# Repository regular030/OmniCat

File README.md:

# OMNICAT

For millions of us, Octocat has been a staple part of our lives, a hardworking and cheerful best friend. What would be more wonderful than to extend that friendship to the real world.
Go check out the journal for our progress and watch our youtube demo here!: https://www.youtube.com/watch?v=gtOdOln78Yw

What does omnicat do?

Feature 1: RC Car
Omnicat is a 4 wheel drive RC car that can be steered either by a traditional game controller or asynchronously through a Leap Motion Sensor with the gesture tracking bindings demonstrated in the video:
Open palm: forward; Fist: backward; Pointer: right; Peace: left; Hang Ten: mode switch

Feature 2: Git Desk Decoration
The OLED on the back displays live details about your Github that are important for easy access, such as number of stars or pull requests on a target repository. You can switch through the display modes using your controller/depth sensor.

Hello! This is our submission project for Hack Club's Highway Hackathon at Github HQ.
With the mission to build something intricate, wacky and helpful, we decided to build a personal home assistant: none other than Octocat itself!

## Wiring Diagram:

## File Structure:
- CAD
  - CAD/F3D Files for the project
- Firmware
  - The Firmware for this project
- new cad
  - STL and 3MF files for the chassis
 - Unity
   -  Unity files for hand Tracking

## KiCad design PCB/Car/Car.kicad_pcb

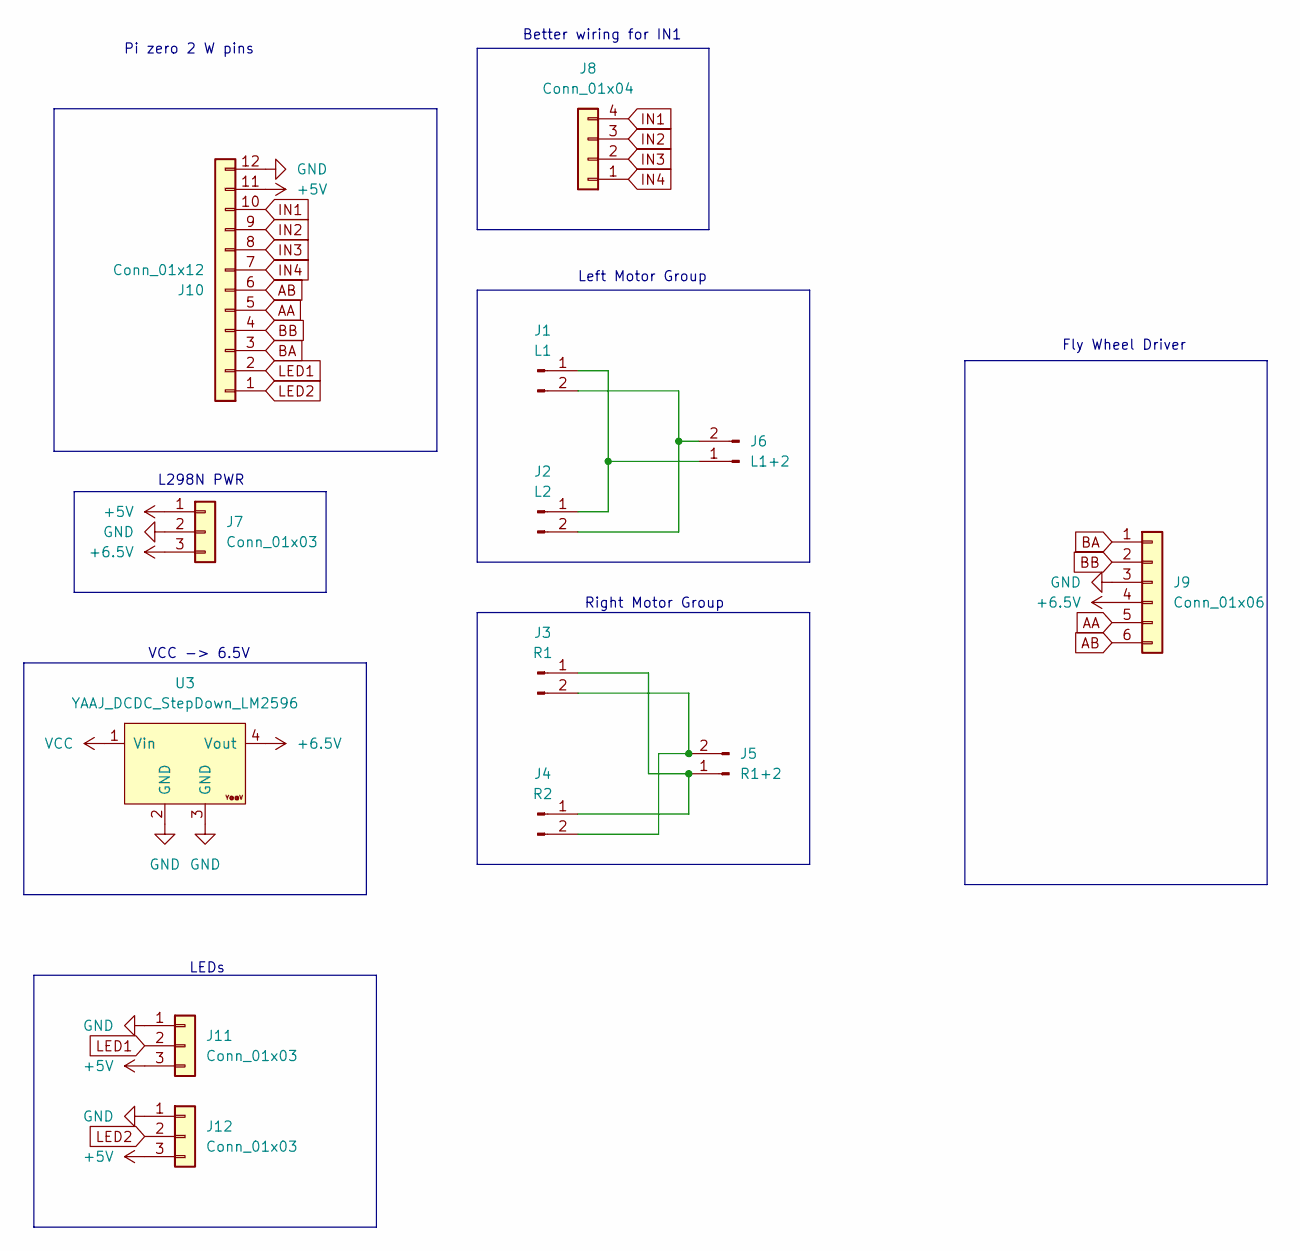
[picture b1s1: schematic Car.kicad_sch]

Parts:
J1: L1; JST 1x2
J2: L2; JST 1x2
J3: R1; JST 1x2
J4: R2; JST 1x2
J5: R1+2; JST 1x2
J6: L1+2; JST 1x2
J7, J11, J12: Conn_01x03; JST 1x3
J8: Conn_01x04; JST 1x4
J9: Conn_01x06; JST 1x6
J10: Conn_01x12; JST 1x12
U3: YAAJ_DCDC_StepDown_LM2596

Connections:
+5V: J7.1, J10.11, J11.3, J12.3
+6.5V: J7.3, J9.4, U3.4 (Vout)
AA: J9.5, J10.5
AB: J9.6, J10.6
BA: J9.1, J10.3
BB: J9.2, J10.4
GND: J7.2, J9.3, J10.12, J11.1, J12.1, U3.2 (GND), U3.3 (GND)
IN1: J8.4, J10.10
IN2: J8.3, J10.9
IN3: J8.2, J10.8
IN4: J8.1, J10.7
LED1: J10.2, J11.2
LED2: J10.1, J12.2
unnamed: J1.1, J2.1, J6.1
unnamed: J1.2, J2.2, J6.2
unnamed: J3.1, J4.1, J5.1
unnamed: J3.2, J4.2, J5.2
VCC: U3.1 (Vin)

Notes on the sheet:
Better wiring for IN1
Left Motor Group
Pi zero 2 W pins
Right Motor Group
VCC -> 6.5V
LEDs
L298N PWR
Fly Wheel Driver

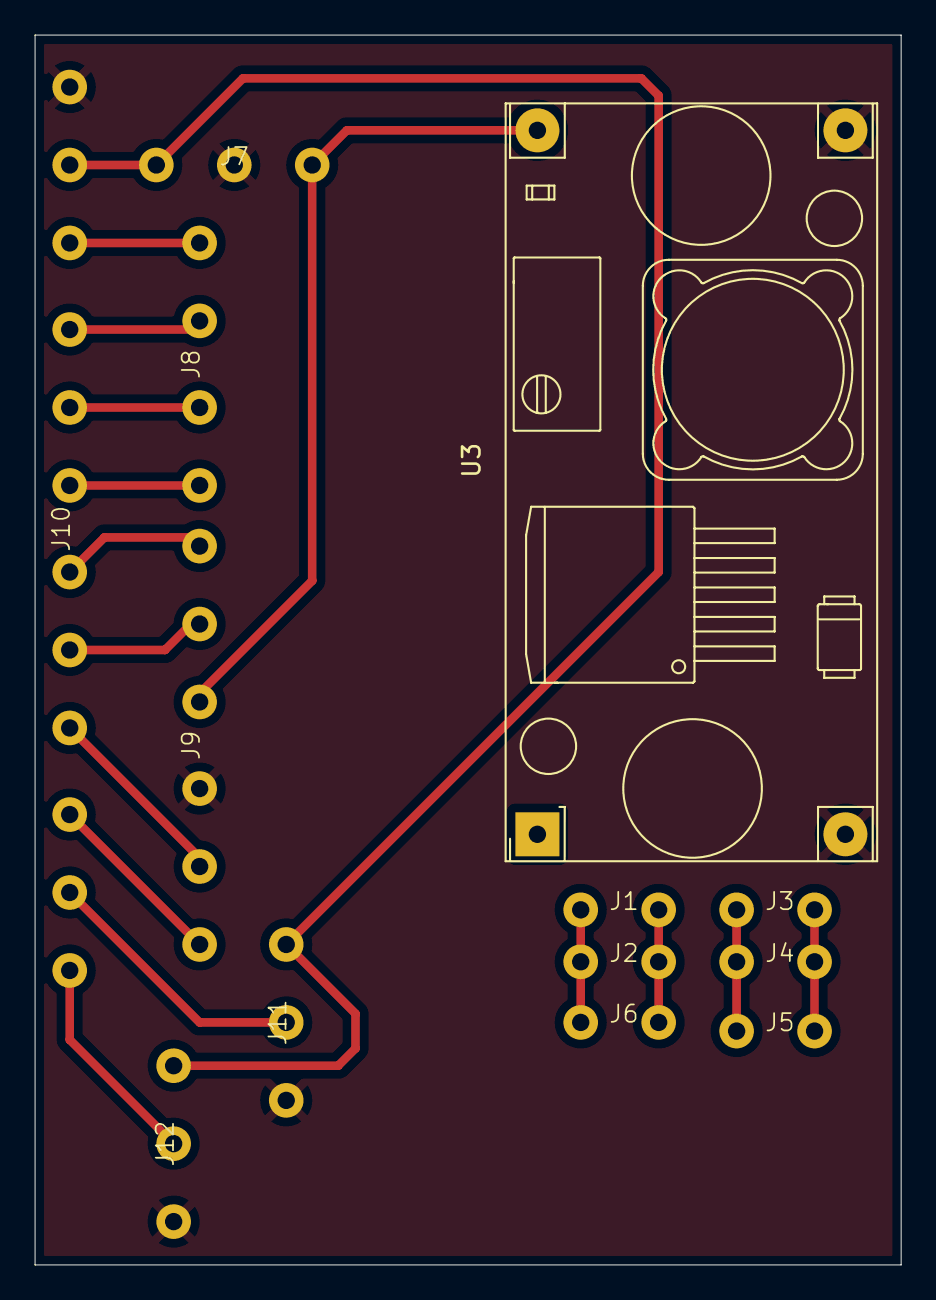
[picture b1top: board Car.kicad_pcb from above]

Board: 2 copper layers, 50.0 x 71.0 mm, 13 parts (0 on the bottom side), 17 nets.

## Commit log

2025-07-12 added pcb
2025-07-12 added firmware, updated pcb
2025-07-12 moved f3d files to CAD
2025-07-12 updated CAD + PCB
2025-07-12 finish PCB
2025-07-12 updated firmware
2025-07-13 updated pcb :D
2025-07-13 updated gbr
2025-07-13 update gbr pt2
2025-07-13 add files
2025-07-13 replace faulty
2025-07-13 push
2025-07-13 adding doc
2025-07-13 Cad + 3mf files
2025-07-13 comb
2025-07-13 corrected function
2025-07-13 moved control to init
2025-07-13 remove silent exit
2025-07-13 check loop
2025-07-13 better messaging
2025-07-13 reqs
2025-07-13 adjust
2025-07-13 push yay
2025-07-13 updated comb2 + added 3mf files
2025-07-14 add yay github
2025-07-14 commit all
2025-07-14 better prints
2025-07-14 journaling
2025-07-14 added unity files (LTS 2022)
2025-07-21 update unity
2025-07-21 deleted unused items
